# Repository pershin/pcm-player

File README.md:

# PCM Player

Pulse-width modulation (PWM) audio player on ATmega328P-PU

## Requirements

### SD card

SDHC 2-32GB must be formatted to FAT32

### Audio files

Property          | Value
------------------|----------------------------
| Format:         | Unsigned 8-bit PCM (RAW)  |
| Sample rate:    | 44100 Hz                  |
| Channels:       | 2                         |
| File extension: | *.PCM                     |

#### Convert FLAC to PCM with FFmpeg

```bash
ffmpeg -i 'example.flac' -ar 44100 -acodec pcm_u8 -f u8 -ac 2 'EXAMPLE.PCM'
```

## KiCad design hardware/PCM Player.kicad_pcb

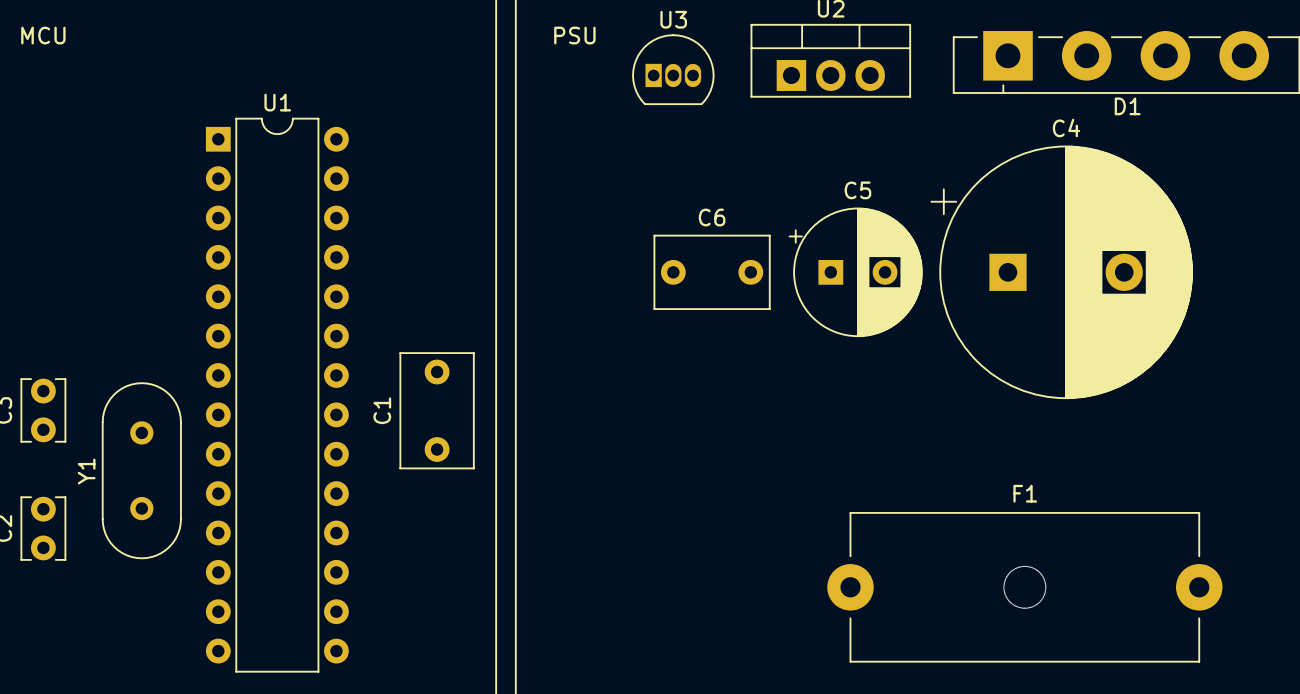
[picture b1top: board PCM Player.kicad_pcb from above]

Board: 2 copper layers, 16 parts (0 on the bottom side), 6 nets, no tracks yet.

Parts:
C1, C6: 1u; C_Rect_L7.2mm_W4.5mm_P5.00mm_FKS2_FKP2_MKS2_MKP2
C2, C3: 22p; C_Disc_D3.8mm_W2.6mm_P2.50mm
C4: 4700u; CP_Radial_D16.0mm_P7.50mm
C5: 100u; CP_Radial_D8.0mm_P3.50mm
D1: GBU808; Diode_Bridge_Vishay_GBU
F1: 250V 4A; Fuseholder_Cylinder-5x20mm_Schurter_0031_8201_Horizontal_Op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
H1, H2, H3, H4: MountingHole; MountingHole_3.2mm_M3
U1: ATmega328P-PU; DIP-28_W7.62mm
U2: LM1085-5.0; TO-220-3_Vertical
U3: LP2950-3.3_TO92; TO-92_Inline
Y1: 16MHz; Crystal_HC49-U_Vertical

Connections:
+3V3: C6.1, U3.1
+5V: C1.1, C5.1, U1.7, U1.20, U2.2, U3.3
GND: C1.2, C2.2, C3.2, C4.2, C5.2, C6.2, D1.4, U1.8, U1.22, U2.1, U3.2
unnamed: C2.1, U1.10, Y1.1
unnamed: C3.1, U1.9, Y1.2
VCC: C4.1, D1.1, U2.3

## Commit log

2020-05-10 Fixed sd_read
2020-05-11 Added F_CPU
2020-05-11 Added comments
2020-05-11 Removed unused variable
2020-05-11 Calc value for OCR1A
2020-05-22 Added PSU
2020-05-22 HC49-U
2020-05-22 Updated PCB
2020-06-13 Added Makefile
2020-07-14 Added amplifier schematic
